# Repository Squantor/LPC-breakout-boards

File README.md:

# LPC microcontroller breakout boards
This is a small collection breakout boards for various LPC microcontrollers, in the future I might add others to the mix. Currently there are a set of eagle and kicad designs, the eagle designs are legacy and might get replaced in the future as currently I am fully comitting on using kicad.
## checkout notes
This repository contains a few submodules, so after checking out do not forget to also check out the submodules.
```
git clone https://github.com/Squantor/LPC-breakout-boards.git
git submodule init
git submodule update
```
Submodules are my private kicad library that are used in my projects. I do try to use the kicad components as much as possible but for certain component types they are less then optimal.

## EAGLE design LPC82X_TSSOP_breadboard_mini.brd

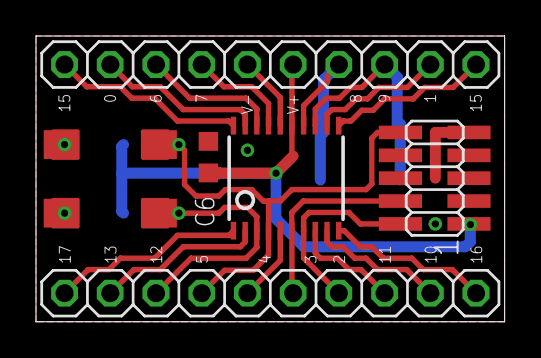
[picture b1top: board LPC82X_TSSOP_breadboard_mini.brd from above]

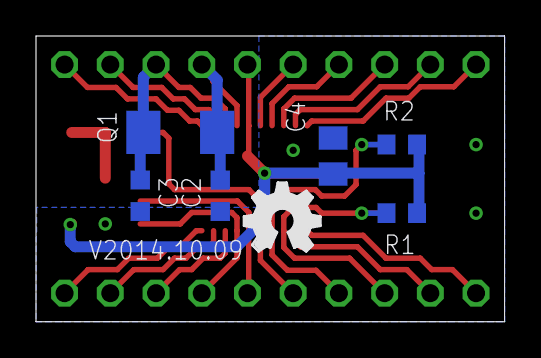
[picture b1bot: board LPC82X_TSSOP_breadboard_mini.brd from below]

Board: 2 copper layers, 26.0 x 15.9 mm, 16 parts (7 on the bottom side), 20 nets.

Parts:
C2, C3: 22p; C0603K
C4: 1u; C0805K
C6: 100n; C0603K
JP1, JP2: 1X10_NORMAL_OCT
JP3: JTAG; 2X05_1.27_SMD
LOGO2: OSHW_LOGO_FILLX0150-NT; OSHW_FILLX150_NOTEXT
LPC812: LPC812M101JDH20; TSSOP20
Q1: 12MHz; CRYSTAL_5.0X3.2
R1, R2: 10k; R0603
U$1, U$2: TACT_2PINDTSM3; DTSM3
U$3, U$4: TACT_2PIN; TD-85XU

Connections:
PIO0_0: JP2.9, LPC812.19
PIO0_1: JP2.2, LPC812.12
PIO0_2: JP1.7, JP3.2, LPC812.7
PIO0_3: JP1.6, JP3.4, LPC812.6
PIO0_4: JP1.5, LPC812.5
PIO0_5: JP1.4, JP3.10, LPC812.4, R2.2, U$1.P$1, U$3.P$1
PIO0_6: JP2.8, LPC812.18
PIO0_7: JP2.7, LPC812.17
PIO0_8: C2.1, JP2.4, LPC812.14, Q1.1
PIO0_9: C3.1, JP2.3, LPC812.13, Q1.2
PIO0_10: JP1.9, LPC812.9
PIO0_11: JP1.8, LPC812.8
PIO0_12: JP1.3, LPC812.3, R1.2, U$2.P$1, U$4.P$1
PIO0_13: JP1.2, LPC812.2
PIO0_14: JP2.10, LPC812.20
PIO0_15: JP2.1, LPC812.11
PIO0_16: JP1.10, LPC812.10
PIO0_17: JP1.1, LPC812.1
VDD: C4.1, C6.1, JP2.5, JP3.1, LPC812.15, R1.1, R2.1
VSS: C2.2, C3.2, C4.2, C6.2, JP2.6, JP3.3, JP3.5, JP3.9, LPC812.16, U$1.P$2, U$2.P$2, U$3.P$2, U$4.P$2

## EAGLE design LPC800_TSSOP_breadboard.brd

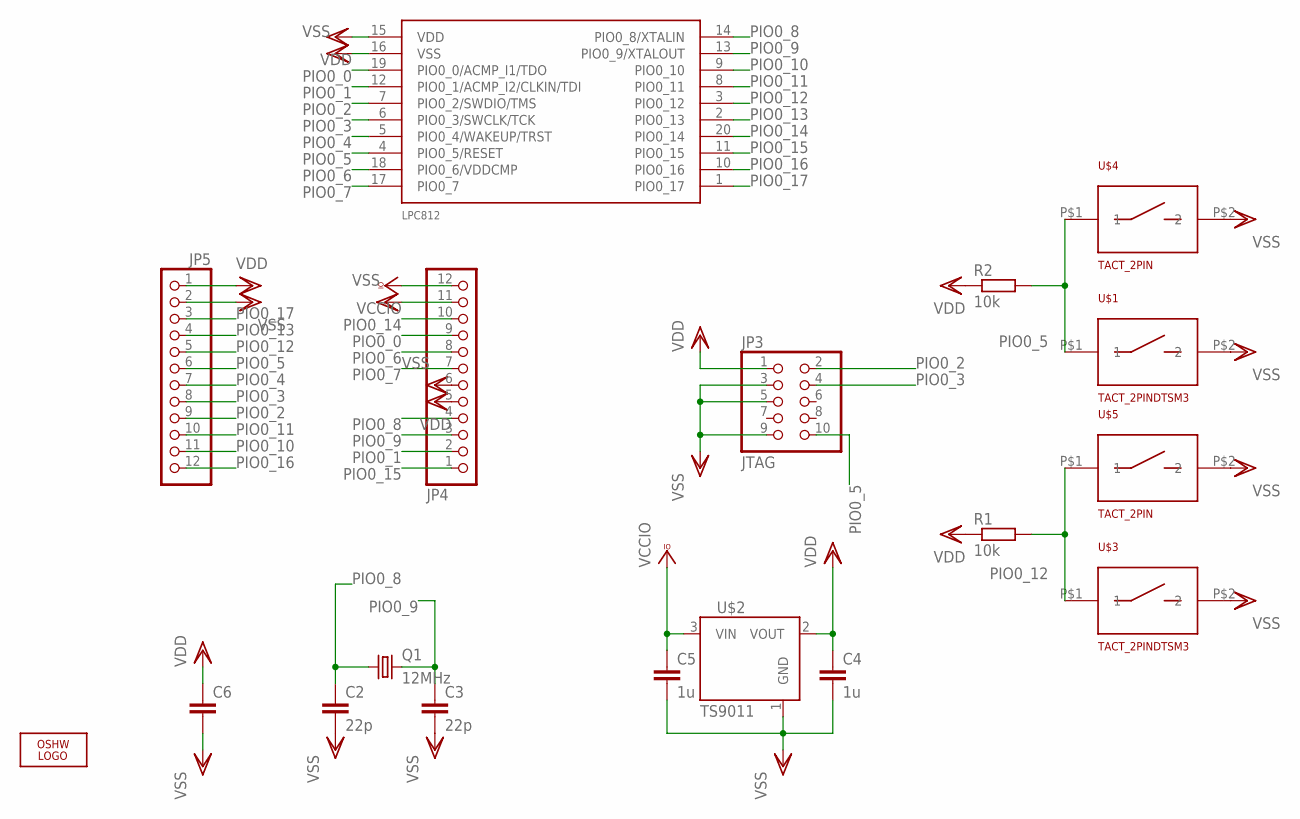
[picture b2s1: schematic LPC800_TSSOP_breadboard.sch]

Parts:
C2, C3: 22p; C0603K
C4, C5: 1u; C0805K
C6: C-EUC0603K; C0603K
JP3: JTAG; 2X05_1.27_SMD
JP4, JP5: PINHD-1X12NORM_OCT; 1X12_NORMAL_OCT
LOGO2: OSHW_LOGO_FILLX0150-NT; OSHW_FILLX150_NOTEXT
LPC812: LPC812M101JDH20; TSSOP20
Q1: 12MHz; CRYSTAL_5.0X3.2
R1, R2: 10k; R0603
U$1, U$3: TACT_2PINDTSM3; DTSM3
U$2: TS9011; SOT23-3
U$4, U$5: TACT_2PIN; TD-85XU

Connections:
PIO0_0: JP4.9, LPC812.19 (PIO0_0/ACMP_I1/TDO)
PIO0_1: JP4.2, LPC812.12 (PIO0_1/ACMP_I2/CLKIN/TDI)
PIO0_2: JP3.2, JP5.9, LPC812.7 (PIO0_2/SWDIO/TMS)
PIO0_3: JP3.4, JP5.8, LPC812.6 (PIO0_3/SWCLK/TCK)
PIO0_4: JP5.7, LPC812.5 (PIO0_4/WAKEUP/TRST)
PIO0_5: JP3.10, JP5.6, LPC812.4 (PIO0_5/RESET), R2.2, U$1.P$1 (1), U$4.P$1 (1)
PIO0_6: JP4.8, LPC812.18 (PIO0_6/VDDCMP)
PIO0_7: JP4.7, LPC812.17 (PIO0_7)
PIO0_8: C2.1, JP4.4, LPC812.14 (PIO0_8/XTALIN), Q1.1
PIO0_9: C3.1, JP4.3, LPC812.13 (PIO0_9/XTALOUT), Q1.2
PIO0_10: JP5.11, LPC812.9 (PIO0_10)
PIO0_11: JP5.10, LPC812.8 (PIO0_11)
PIO0_12: JP5.5, LPC812.3 (PIO0_12), R1.2, U$3.P$1 (1), U$5.P$1 (1)
PIO0_13: JP5.4, LPC812.2 (PIO0_13)
PIO0_14: JP4.10, LPC812.20 (PIO0_14)
PIO0_15: JP4.1, LPC812.11 (PIO0_15)
PIO0_16: JP5.12, LPC812.10 (PIO0_16)
PIO0_17: JP5.3, LPC812.1 (PIO0_17)
VCCIO: C5.1, JP4.12, U$2.3 (VIN)
VDD: C4.1, C6.1, JP3.1, JP4.5, JP5.1, LPC812.15 (VDD), R1.1, R2.1, U$2.2 (VOUT)
VSS: C2.2, C3.2, C4.2, C5.2, C6.2, JP3.3, JP3.5, JP3.9, JP4.6, JP4.11, JP5.2, LPC812.16 (VSS), U$1.P$2 (2), U$2.1 (GND), U$3.P$2 (2), U$4.P$2 (2), U$5.P$2 (2)

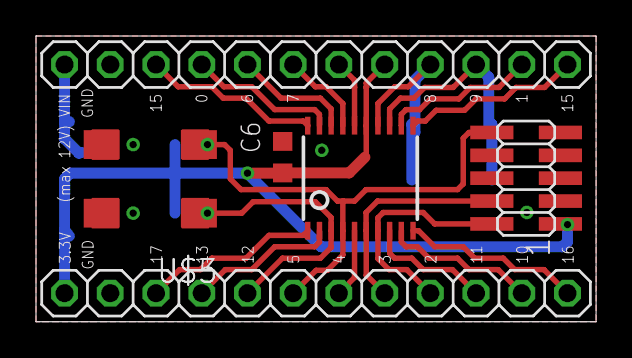
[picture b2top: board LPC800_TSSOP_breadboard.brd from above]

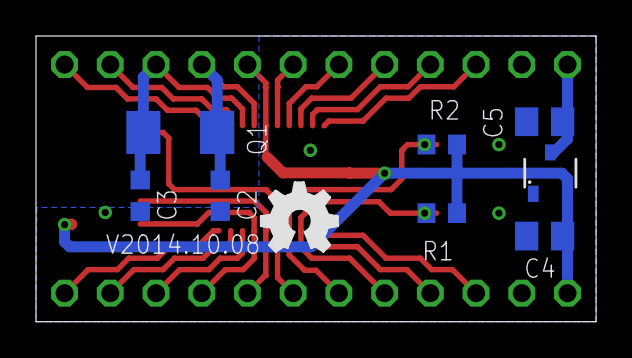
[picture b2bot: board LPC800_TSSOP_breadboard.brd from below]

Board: 2 copper layers, 31.1 x 15.9 mm, 18 parts (9 on the bottom side), 21 nets.

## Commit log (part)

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2014-04-18 Update README.md
    * Added more clear description and TODO list
2014-04-18 * populating with BRD and SCH files
2014-04-18 * added eagle project file
2014-04-18 * small updates
2014-04-18 * small mods
2014-04-23 Update README.md
    * Improve layout
    * added more TODO's
    * added link to OSHpark and credit inspirational page
    * added status updates
2014-04-24 * small fixes on TODO list
2014-04-24 * updated todo
2014-04-25 * doing some TODO's
2014-04-30 * updated board and schem with todo's
2014-04-30 * updated readme
2014-05-01 * small beautification mods
2014-05-11 * minor updates with silk, pinout documentation, hole expansion
2014-05-13 Update README.md
    Updated status header
2014-05-16 Update README.md
    updated pricing and TODO's
2014-05-29 * small modifications * improved regulator decoupling capacitor position to leave more space for the pinheaders * improved crystal positioning to leave more space for the pinheaders
2014-06-08 * added some pictures and updated the readme
2014-06-23 * Added image exports of schematics and PCB layers
2014-06-24 Update README.md
    Small mod
2014-06-24 Update README.md
    * Added more to do actions
2014-08-11 Update README.md
    * added a few TODO's
2014-09-26 * added low cost lpc812 breadboard breakout (mini)
2014-09-28 * finished LPC800 mini board * fixed pin 1 for JTAG connection - TODO: Printout inspection and checks for the button layout
2014-10-08 * updated boards with cheaper buttons, better layout and indexed JTAG header
2014-10-09 * small changes preparing for commit to OSH park
2014-10-09 * added final bits and pieces * updated readme
2015-02-20 * renamed LPC800 references to LPC81X * started with LPC82X boards, still need to add the MLF style packages
2015-02-26 * started with lpc824 TSSOP breakout
2015-11-22 * fixed some small mistakes
2015-11-22 * project file updates
2017-01-07 * big cleanup/move of files
2017-01-07 * added gitignore file
2017-01-07 * added kicad starts for the LPC824 breakouts
2017-01-09 * added some file ignore wildcards for kicad
2017-01-09 * small updates to the LPC824 breakouts
2017-01-12 * modified eagle project to 7.4
2017-01-12 * updated LPC824 breakout
2017-01-12 * small schematic updates
2017-01-23 * fully connected up connectors - next JTAG connection
2017-01-23 * further layout of the LPC824 chip
2017-03-21 * added a few parts to the LPC824 breakout
2017-03-21 * completed breakout board schematic * started with layout of breakout
2017-03-25 * updated documentation
2017-03-25 * added root readme
2017-03-25 * added documentation
2018-10-26 time to update this project and revisit most of the boards with new insights
2018-10-26 Update README.md
    Whoops, backticks needed for codeblocks
2018-10-26 Update README.md
    Fixing another problem
2018-10-26 regenerated kicad projects with submodule
2018-10-26 started on LPC824 QFN33 breakout
2018-10-26 started with schematic entry of QFN33 LPC824 breakout
2018-10-26 more schematic updates updated footprint of a used button
2018-10-26 updated with solder jumper schematic symbols added some jumpers to the QFN33 breakout
2018-10-26 finished schematic updated new footprints from submodule
2018-10-26 further pcb placement
2018-10-27 started with first layout
2018-10-27 finished routing tracks
2018-10-28 added LPC824 QFN33 breakout on two layers (quicker production) added readme
2018-10-28 differentiating rename from 4 layer to 2 layer
2018-10-28 rename action to explicitly mention layercount
2018-10-28 added bulk decoupling 0805 increased clearance of ground plane
2018-10-28 silk screen updates
2018-10-28 updated versionnumber
2018-10-28 added schematic
2018-10-29 removed absolute path
2018-10-29 removed some parts from schematics to simplify the breakout
2018-10-29 updated schematic bits updated board and rerouted with some deletions, lets see if we can shrink the board a bit
2018-10-30 reduced PCB size, rerouting large parts of it
2018-10-31 updated with new library with jumpers
2018-10-31 updated schematic, added VDD jumper, added top groundplane, completed layout
2018-10-31 updated pcb and fixed some inconsistencies
2018-11-02 some minor trace moves
2018-11-02 updated version number
2018-11-02 added schematic and PCB plots
2018-11-02 pcb update
2018-11-04 copied over schematic, updated libraries
2018-11-04 schematic updates
2018-11-04 updated library references
2018-11-06 updated newer version of PCB library
2018-11-06 updated new libraries
2018-11-06 completed schematic
2018-11-06 updated readme documentation
2018-11-06 started initial PCB layout
2018-11-09 initial component placement
2018-11-09 component placement done
2018-11-09 intermediate layout checkin
2018-11-09 layout done, positioning silk labels
2018-11-09 updated pcb lib
2018-11-09 updated LPC824 component
2018-11-09 updated to new component
2018-11-09 silk placement done
2018-11-09 added schematic plot and PCB gerbers
2018-11-09 adding zips to ignore
2018-11-09 updated a few traces and silk screen bits
2018-11-09 updated PCB library
2018-11-09 updated PCB and plots
2018-11-10 small silk updates, updated values, top groundplane
2018-11-10 updated all plots
2018-11-10 updated readme with newer project
2018-11-21 added paste layers and regenerated gerbers
2018-11-21 updated gerbers, updated generation preferences
2018-11-22 fixed incorrect crystal footprint
2018-11-22 changed via annular rings to 200microns
2018-11-22 updated plots for production
2018-11-22 updated silk mistakes
2018-11-23 updated status
2018-11-23 fixed DRC error on PCB, fixed resistor positions, updated versionnumber
2018-11-23 updated LPC824 QFN33 gerber and schematic plot
2018-11-24 updated versionnumber, fixed unrouted trace
2018-11-24 updated plots
2018-11-25 linked to shared project on OSHpark
2019-01-18 fixed incorrect crystal footprint and relayout
2019-01-18 added some project photos
2019-01-19 newer lpc library
2019-01-19 small trace change, updated version number
2019-01-20 fixed mistake in microcontroller power, updated library component, added newer component library, rerouted
2019-01-21 updated silkscreen
2019-01-21 run DRC
2019-02-15 added first automated board test project
2019-02-15 added LPCopen library for the lpc824
2019-02-15 added lpcopen library to makefile
2019-02-15 added all the needed stuff for blinky
2019-02-15 blinky implemented
2019-02-15 WIP pin test algorithm, added udiv routine
2019-02-15 first testing GPIO works, now to fix all the TODO's
2019-02-15 added explanation for the maximum transition time derivations
2019-02-15 added some delays, need to fix this more nicely
2019-02-15 changed to proper gpio iocon pair type for testing
2019-02-15 added additional check so we never get stuck forever waiting
2019-02-15 added readme explaing what software exists for the breakouts
2019-02-15 newer lpcxpresso library
2019-02-15 updated readme on the LPC82X TSOP20 breakout
2019-02-15 removing old defunct project
2019-02-15 fixed typo in image link
2019-02-15 fixed mistakes in Readme
2019-03-09 reorganising repo
2019-03-09 added LPC112X and LPC81X breakouts
2019-03-10 rename action for LPC82X QFN33 breakout
2019-03-10 more renames
2019-03-10 more renames!
2019-03-10 copied over LPC824 to LPC812
2019-03-10 update submodule
2019-03-10 updated pcb library, replaced LPC824 with LPC812
2019-03-10 added named connector for breakout
2019-03-10 WIP PCB layout
2019-03-10 layout completed
2019-03-10 silk layout completed
2019-03-10 various beauty changes
2019-03-10 copied LPC824 breakout to LPC1125
2019-03-10 schematic entry in progress, added LPC1125
2019-03-11 final small changes to PCB
2019-03-11 fixed mistake with shrunk groundplane, updated readme
2019-03-13 newer LPC812 schematic component, changed paste vs pad
2019-03-13 LPC824 QFN33 new footprint for LPC and shrunk paste size
2019-03-29 updated open drain reason
2019-03-29 updated test software with newer template
2019-03-29 removed defunct files, updated codelite project
2019-03-29 fixing problem with lto
2019-03-31 moving to general purpose breakout tester
2019-03-31 added boards to build system
2019-03-31 moving stuff to board support
2019-03-31 added usb bmp debugging, enable power to jig
2019-03-31 added target power enable/disable commands and scripts
2019-03-31 updated debugging commands, changing build system
2019-03-31 changed breakout name as we have TSSOP20 and QFN33 breakouts
2019-03-31 split up functionality of pin tester
2019-03-31 updated Makefiles
2019-03-31 updated to newer lpc chip
2019-03-31 updated makefiles to support multiple boards
2019-03-31 added LPC81X_JDH20 breakout tests
2019-03-31 fixed problem with lack of division routines in ROM, updated clocking
2019-03-31 gpio tests operational, but still too low timings from Lo to Hi, disabled optimization in Debug
2019-04-04 fixed typo
2019-04-04 fixed bug, reworking pin test algorithm fixed a bug with incorrect MCU selection, pin test algorithm depends too much on gpio characteristics and we dont check both charging slopes
2019-04-04 added TODO for the algorithm, time for sleep
2019-04-09 refactoring and redoing the gpio test routine
2019-04-09 WIP gpio tester
2019-04-09 WIP: completed gpio tester, now testing
2019-04-09 simplified datastructure, increased charge timing
2019-04-09 fine tuned timings
2019-04-10 test routine returns failing GPIO, enabled all pins for LPC812
2019-04-10 fixing failing release build
2019-04-10 cleanup
2019-04-10 updated release debugger settings
2019-04-10 testing LPC82X breakout
2019-04-10 newer PCB library
2019-04-10 added named connectors for LPC82XJDH20 breakout
2019-04-10 ignoring fp-info-cache
2019-04-11 updated silk labels
2019-04-11 changed net names, added named connectors
2019-04-11 pcb net updates
2019-04-11 changed connectors, newer component library
2019-04-12 silk placement completed
2019-04-16 added LPC824 QFN33 ADC evaluator
2019-04-16 updated schematic, partial layout of new planes and reduction of components
2019-04-17 updated to named pcb connectors, further plane addition, inital silk placement
2019-04-24 added embedded library dependency
2019-04-24 added LPC824 tryout, needs cleanup
2019-04-26 newer libEmbeddedC
2019-04-26 tab conversion
2019-04-26 cleanup of project
2019-04-26 more cleanup
2019-04-26 fixed uart output, some cleanup from playground
2019-04-28 changing multi channel sampling
2019-04-28 multi channel sampling, cleanup
2019-04-28 added command prompt to ADC evaluator
2019-05-10 updated libc
2019-05-11 added LPC824 QFN33 testjig PCB project
2019-05-11 routing completed
2019-05-12 schematic addition
2019-05-12 added RED led indicator
2019-05-12 further schematic additions
2019-05-12 further placement of components
2019-05-14 changed silk openings
2019-05-14 silkscreen updates
2019-05-14 updates to paste aperatures, update versionnumber
2019-05-14 fixed weird trace position
2019-05-15 fixed DRC error by updating footprint, rendered plots
2019-05-17 updated libembeddedC
2019-05-21 fixed problem with ADC offset
2019-05-23 reduced sampling rate to improve ADC accuracy
2019-06-18 initial board target for lpc82xJHI33 breakout
2019-06-18 enabled board, defined pins to test
2019-06-18 set board to default to QFN33 board
2019-06-18 reduced lower bound of GPIO test QFN33 test board has 1uF capacitors instead of 2.2uF like the rest, need to update those test jigs
2019-06-18 library updates
2019-06-19 timings to be test jig specific Some jigs have different resistors/capacities
2019-06-19 fine tuned max and min for high low and low high transitions for LPC824JH33 breakouts
2019-06-19 fixed bug that you would never fail on maximum timeouts
2019-06-19 finetuned values for high low and low high maximum and minimum timings
2019-07-10 updated to newer command library
2019-07-10 moved SWD connector to a subschematic
2019-07-10 needed relayout as moving stuff off sheet will reset it
2019-07-10 started with submodules
2019-07-10 updated submodule to include SWD subschematic
2019-07-17 updated to newer LPC824 schematic component
2019-07-19 fixed incorrect path for schematic library
2019-07-19 removing defunc library
2020-07-20 started on LPC812 XSON16 breakout
2020-07-20 updated gitignore with newer files
2020-07-20 WIP schematic definition and raw component placement
